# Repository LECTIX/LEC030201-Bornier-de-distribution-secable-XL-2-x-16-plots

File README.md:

# LEC030201 - Bornier de distribution sécable XL – 2 x 16 plots
Fichiers sources pour le produit LEC030201

## Description du produit

- **DISTRIBUTION** Les 16 borniers verts sont tous connectés ensemble, tout comme les 16 borniers bleus. Courant max = 10 A. Tension max = 250 V.
- **SÉCABLE** Coupez les barrettes sur les pointillés pour les séparer en 2 barrettes indépendantes.
- **MARQUEUR** Le module dispose d’une zone blanche dans laquelle il est possible d’indiquer à l’aide d’un feutre la polarité, la tension, ou bien un numéro d’identification propre à vous.
- **APPLICATIONS** Utilisez ces barrettes de distribution pour connecter facilement une alimentation à plusieurs dispositifs (éclairage, modules, …).

## Utiliser les fichiers sources pour fabriquer le produit

Il n'est **pas nécessaire de savoir souder ou d'être bon en électronique** pour se procurer ce produit. Grâce aux fichiers sources publiés ici, vous pouvez être en mesure de faire fabriquer ce produit par un sous traitant.

### Faire fabriquer chez un sous traitant

Il est aujourd'hui possible de faire fabriquer à moindre cout des cartes électroniques. Nous recommendons [JLCPCB](https://jlcpcb.com/) si vous voulez aller au moins cher. Si vous préférez un acteur européen, [eurocircuits](https://www.eurocircuits.com/) est un des acteurs reconnus.

1. Télécherger les sources de ce produit en cliquant sur le bouton `Code`, puis `Download ZIP`.
1. Décompresser le dossier.
1. Les fichiers pour la fabrication se trouvent dans le répertoire `hardware/prod`.
1. Se connecter sur [https://cart.jlcpcb.com/quote](https://cart.jlcpcb.com/quote)
1. Cliquer sur le bouton `Add gerber file` et sélectionner le fichier `gerbers.zip`.
1. Sélectionnez la quantité de cartes que vous souhaitez dans le champs `PCB Qty`.
1. Laisser toutes les autres options par défaut, puis cliquez sur le toggle switch en face de `PCB Assembly`, et enfin sur le bouton `confirm`.
1. Une preview de la carte électronique sans les composants doit apparaitre. Cliquez sur `NEXT`.
1. Cliquez sur le bouton `Add BOM File`, puis sélectionnez le fichier `bom.csv`
1. Cliquez sur le bouton `Add CPL File`, puis sélectionnez le fichier `pos.csv`
1. **Vérifier que tous les composants sont en stock** et bien sélectionnés, puis cliquez sur `NEXT`.
1. Une preview de la carte avec ses composants apparait. Continuer le chemin en cliquant sur `NEXT`.
1. Le prix final apparait. Sélectionnez la catégorie du produit, puis cliquez sur `SAVE TO CART`.
1. Une fois sauvegardé dans votre panier, vous pouvez valider votre commande et choisir le moyen d'acheminement. Afin de ne pas avoir à se préoccuper des frais de douane, nous vous conseillons de choisir une méthode d'expédition DDP.

Vous receverez vos cartes sous 1 à 3 semaines. 

**Nous ne sommes en aucun cas responsables des cartes qui arriveraient défectueuses ou non fonctionnelles.**

### Modifications des fichiers sources

Installez kicad 6 (ou version supérieure), et ouvrez le fichier LEC030201.kicad_pro

### Regénérer les fichiers gerber, BOM, et position (Optionnel)

Peut se faire simplement en utilisant kikit :

```
cd hardware

# generate assembly files
docker run --rm -w /kikit -v $PWD:/kikit yaqwsx/kikit kikit fab jlcpcb --assembly --no-drc --schematic LEC030201.kicad_sch --field LCSC --corrections JLCPCB_CORRECTION --nametemplate LEC030201_{} LEC030201.kicad_pcb prod/

```

## License
Tous nos fichiers sont plubliés sous la license CERN Open Hardware Licence Version 2 - Strongly Reciprocal

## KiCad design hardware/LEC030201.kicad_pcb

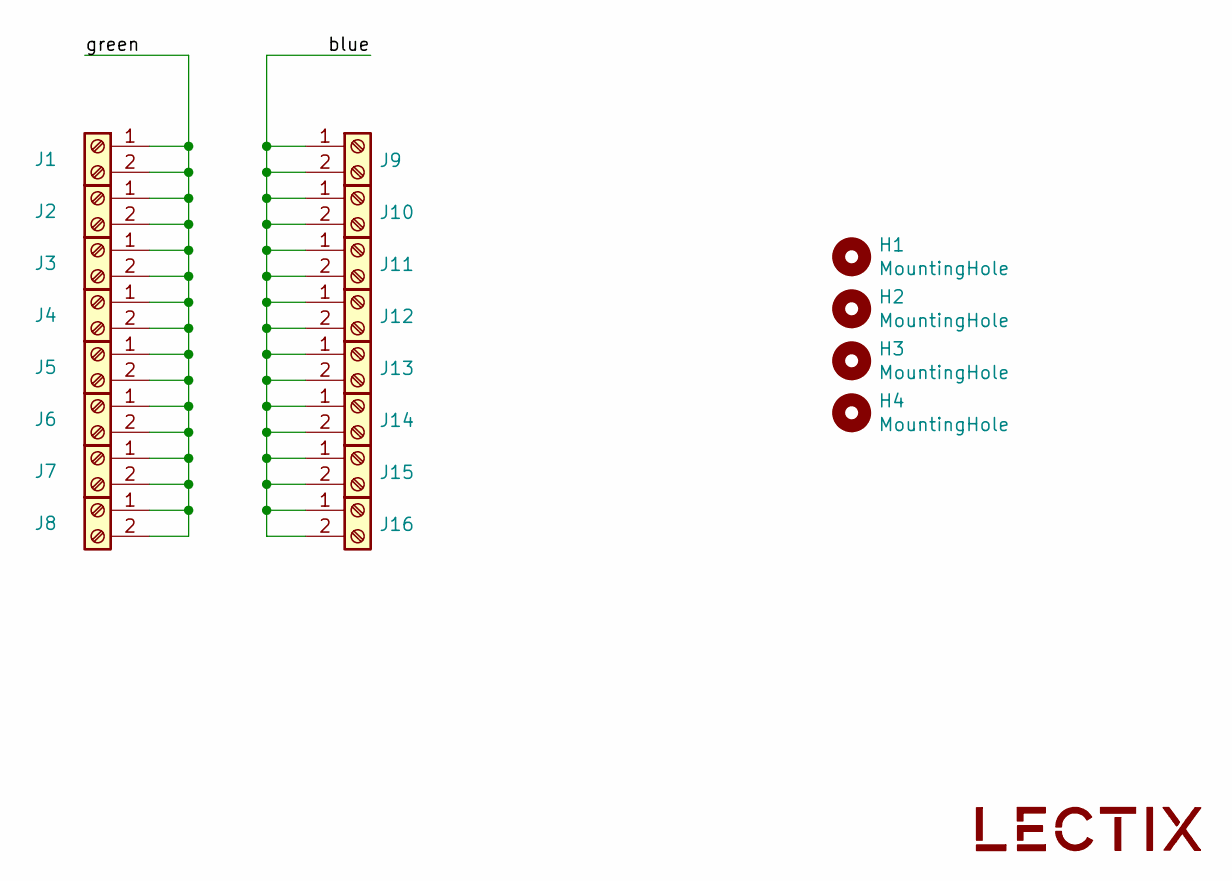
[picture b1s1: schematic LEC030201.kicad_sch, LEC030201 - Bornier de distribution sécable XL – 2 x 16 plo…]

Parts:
H1, H2, H3, H4: MountingHole; MountingHole_3.2mm_M3
J1, J2, J3, J4, J5, J6, J7, J8: Screw_Terminal_01x02_green; TerminalBlock_bornier-2_P5.08mm-green; MPN DB126V-5.0-2P-GN; LCSC C395849
J9, J10, J11, J12, J13, J14, J15, J16: Screw_Terminal_01x02_blue; TerminalBlock_bornier-2_P5.08mm-blue; MPN DB301V-5.0-2P-BU-S; LCSC C395882
LOGO1: logo_lectix_25mm; Logo_10mm

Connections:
/blue: J9.1, J9.2, J10.1, J10.2, J11.1, J11.2, J12.1, J12.2, J13.1, J13.2, J14.1, J14.2, J15.1, J15.2, J16.1, J16.2
/green: J1.1, J1.2, J2.1, J2.2, J3.1, J3.2, J4.1, J4.2, J5.1, J5.2, J6.1, J6.2, J7.1, J7.2, J8.1, J8.2

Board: 2 copper layers, 22 parts (0 on the bottom side), 2 nets, no tracks yet.

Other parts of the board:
kibuzzard-627E8DB1: G***; kibuzzard-627E8DB1

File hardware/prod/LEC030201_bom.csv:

Comment,Designator,Footprint,LCSC
Screw_Terminal_01x02_green,"J1,J2,J3,J4,J5,J6,J7,J8",0_connectors:TerminalBlock_bornier-2_P5.08mm-green,C395849
Screw_Terminal_01x02_blue,"J9,J10,J11,J12,J13,J14,J15,J16",0_connectors:TerminalBlock_bornier-2_P5.08mm-blue,C395882

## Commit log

2023-04-19 Add hardware source files
